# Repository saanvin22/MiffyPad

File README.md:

# MiffyPad
This is a keypad that I made based on Miffy as an accessory, it has all the letters!

https://youtu.be/KvLJUB490SI 

## Schematic

## PCB

## CAD

## BOM:

Here is everything needed to make this hackpad (All parts are part of the approved kit)
- 5x Cherry MX Switches
- 5x DSA Keycaps
- 4x M3x5x4 Heatset inserts
- 4x M3x16mm screws
- 2x SK6812 MINI-E LEDs
- 1x XIAO RP2040
- 2x Printed parts for the case

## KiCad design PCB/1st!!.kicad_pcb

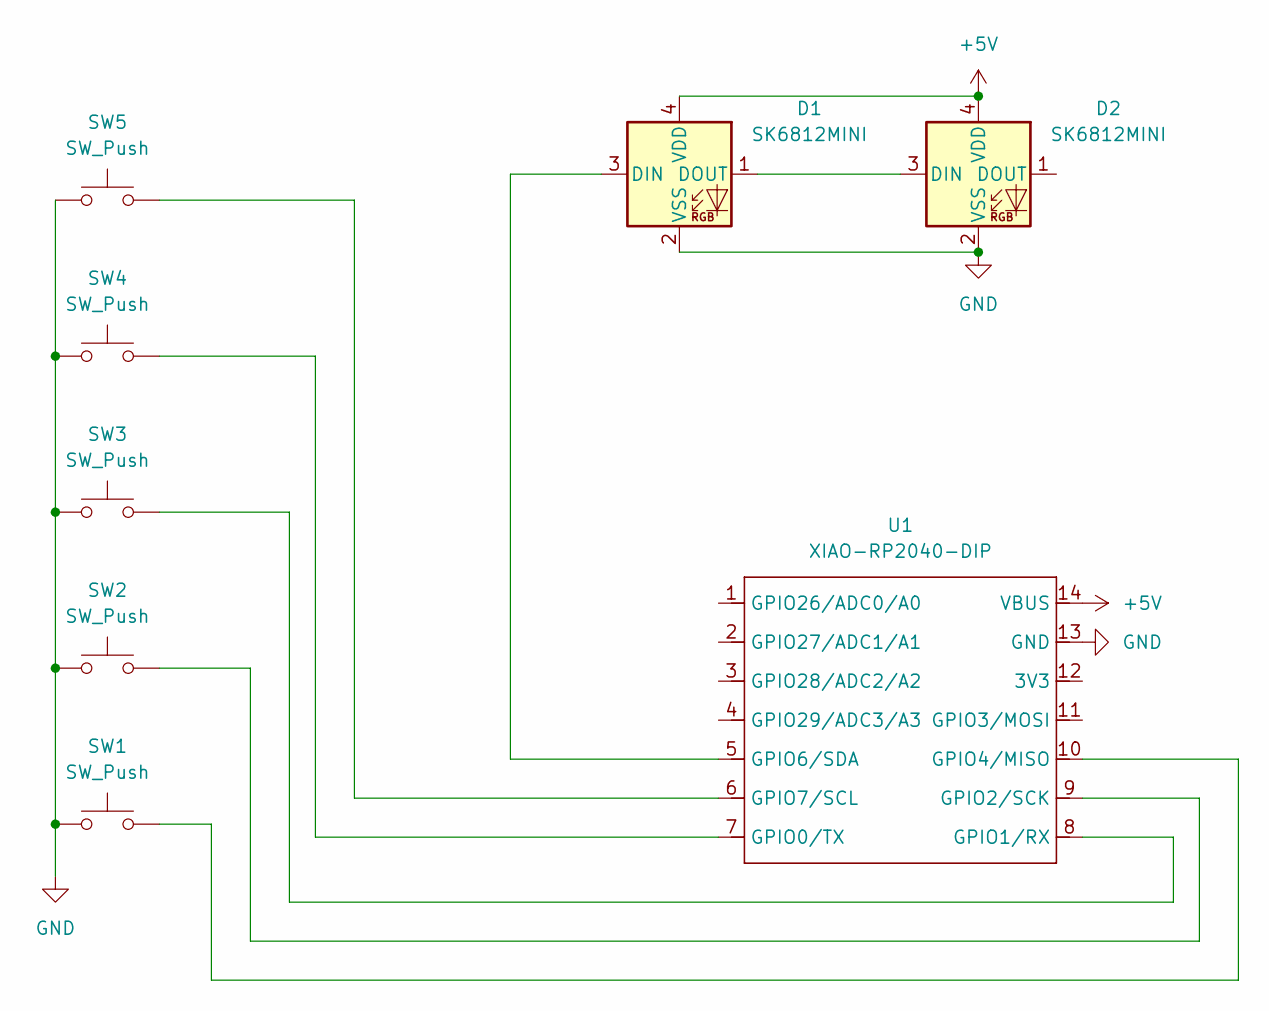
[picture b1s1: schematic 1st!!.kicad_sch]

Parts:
D1, D2: SK6812MINI; LED_SK6812MINI_PLCC4_3.5x3.5mm_P1.75mm
SW1, SW2, SW3, SW4, SW5: SW_Push; SW_Cherry_MX_1.00u_PCB
U1: XIAO-RP2040-DIP

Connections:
+5V: D1.4 (VDD), D2.4 (VDD), U1.14 (VBUS)
GND: D1.2 (VSS), D2.2 (VSS), SW1.1, SW2.1, SW3.1, SW4.1, SW5.1, U1.13 (GND)
unnamed: D1.3 (DIN), U1.5 (GPIO6/SDA)
unnamed: D1.1 (DOUT), D2.3 (DIN)
unnamed: SW4.2, U1.7 (GPIO0/TX)
unnamed: SW3.2, U1.8 (GPIO1/RX)
unnamed: SW2.2, U1.9 (GPIO2/SCK)
unnamed: SW1.2, U1.10 (GPIO4/MISO)
unnamed: SW5.2, U1.6 (GPIO7/SCL)

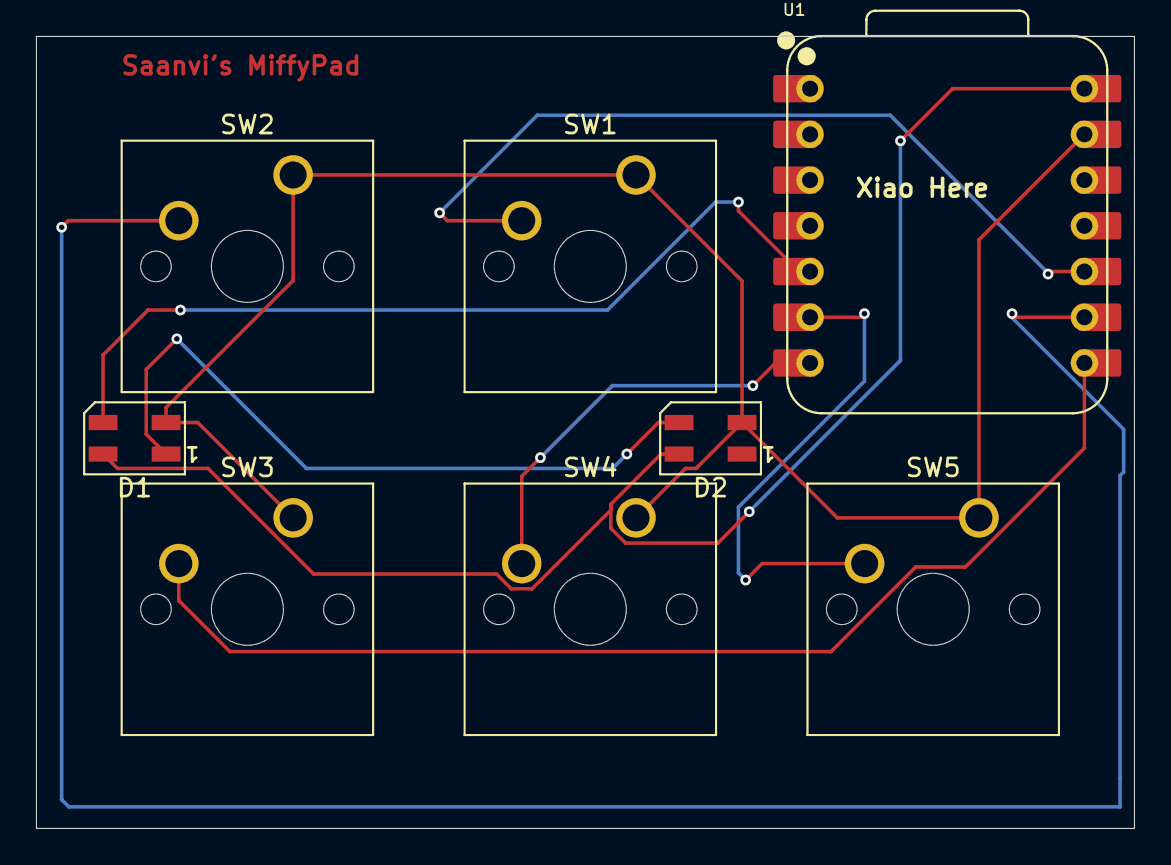
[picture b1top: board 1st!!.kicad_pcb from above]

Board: 2 copper layers, 61.0 x 44.0 mm, 8 parts (0 on the bottom side), 9 nets.
